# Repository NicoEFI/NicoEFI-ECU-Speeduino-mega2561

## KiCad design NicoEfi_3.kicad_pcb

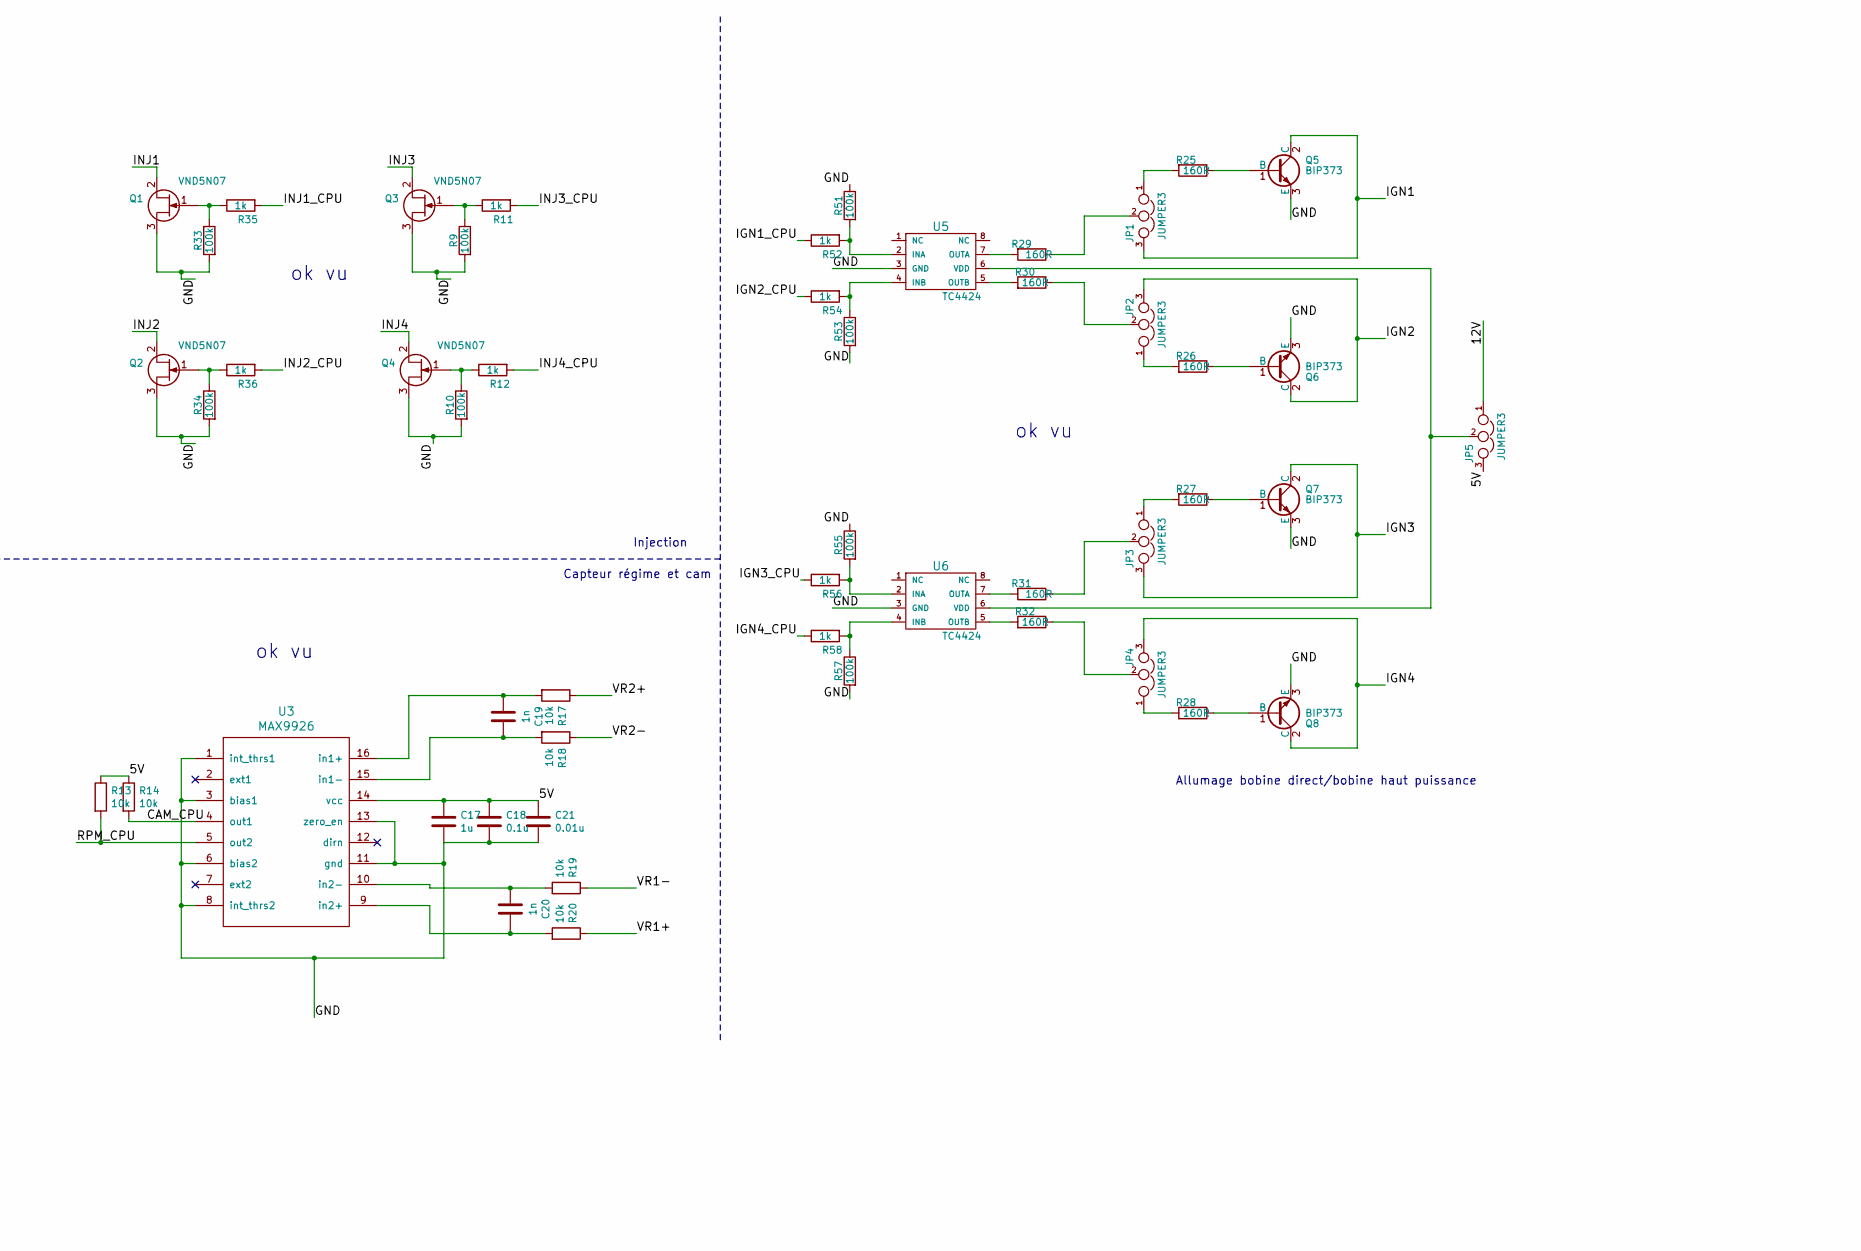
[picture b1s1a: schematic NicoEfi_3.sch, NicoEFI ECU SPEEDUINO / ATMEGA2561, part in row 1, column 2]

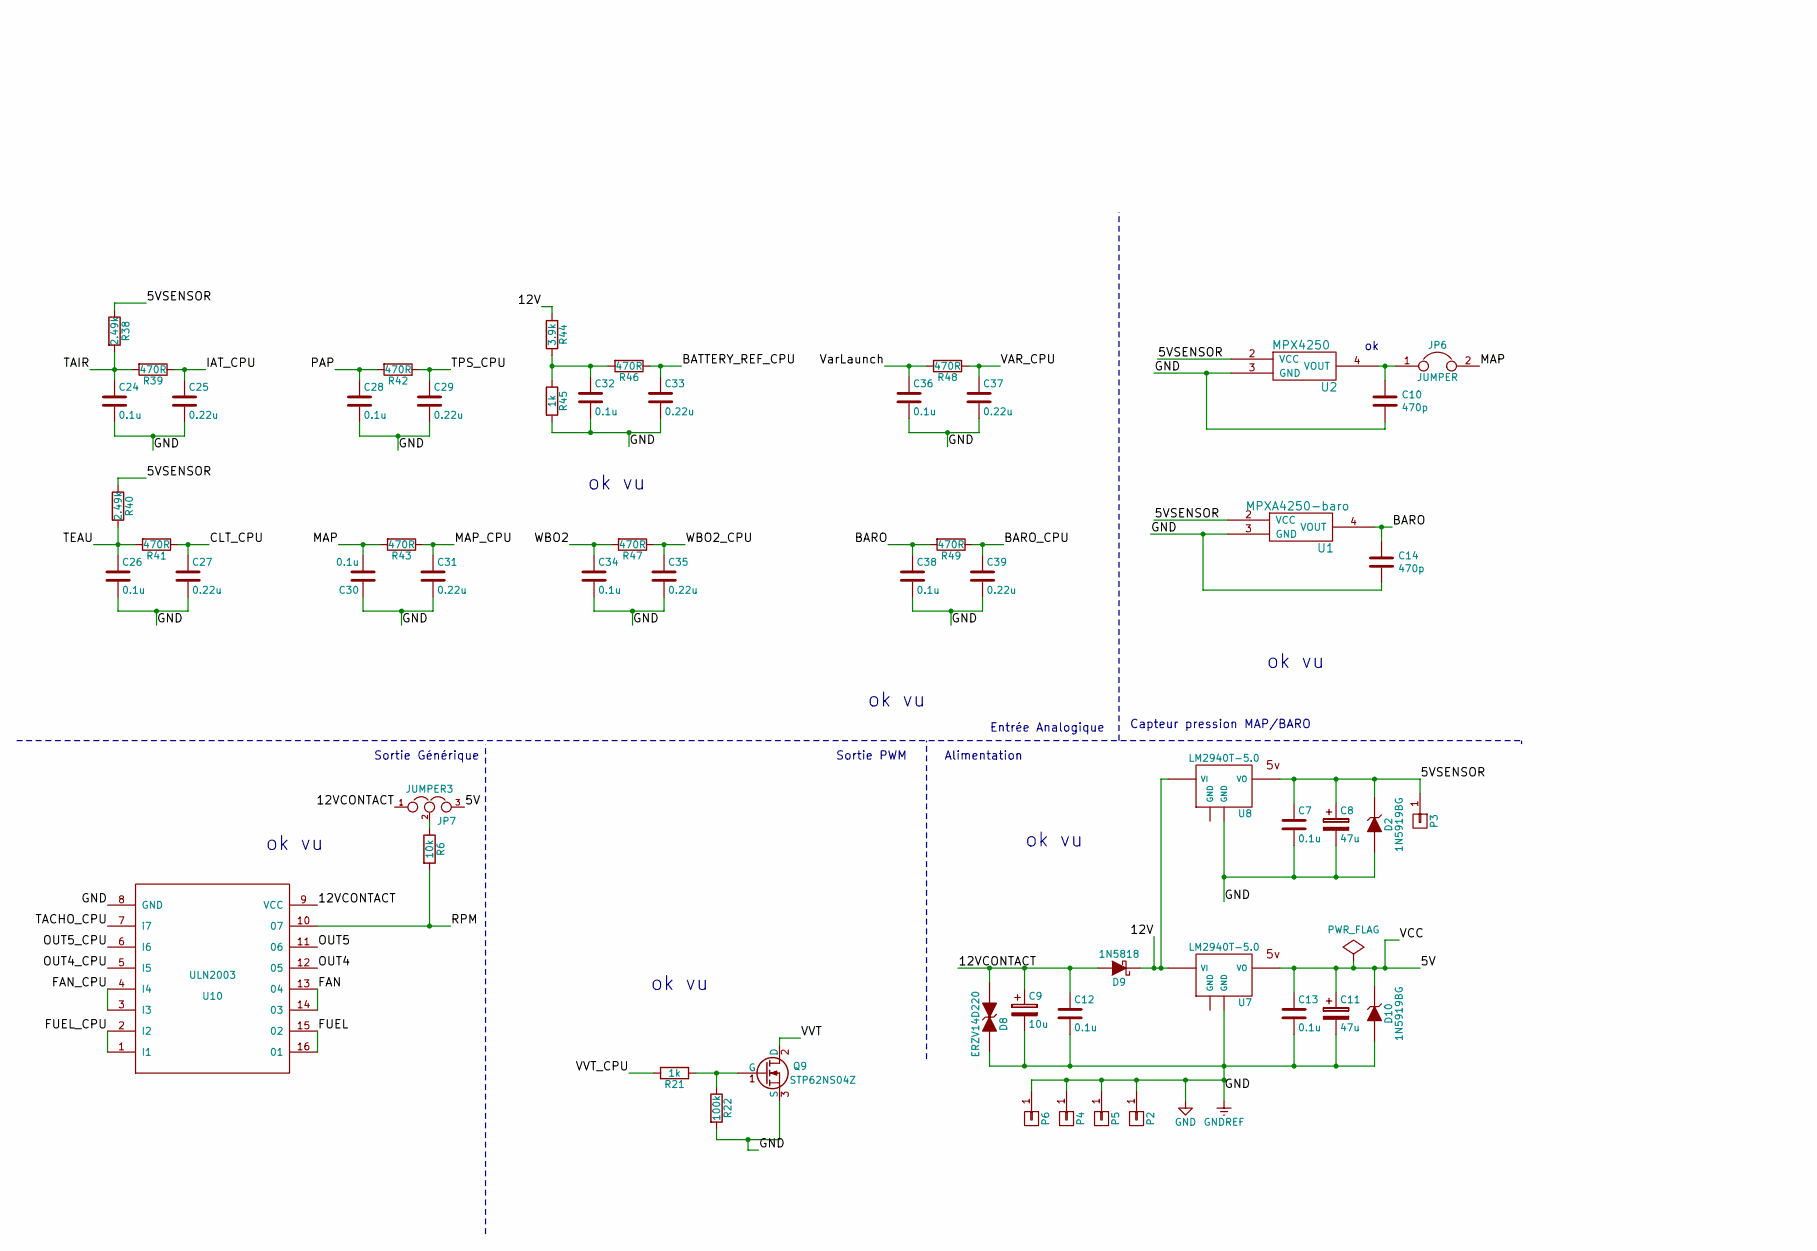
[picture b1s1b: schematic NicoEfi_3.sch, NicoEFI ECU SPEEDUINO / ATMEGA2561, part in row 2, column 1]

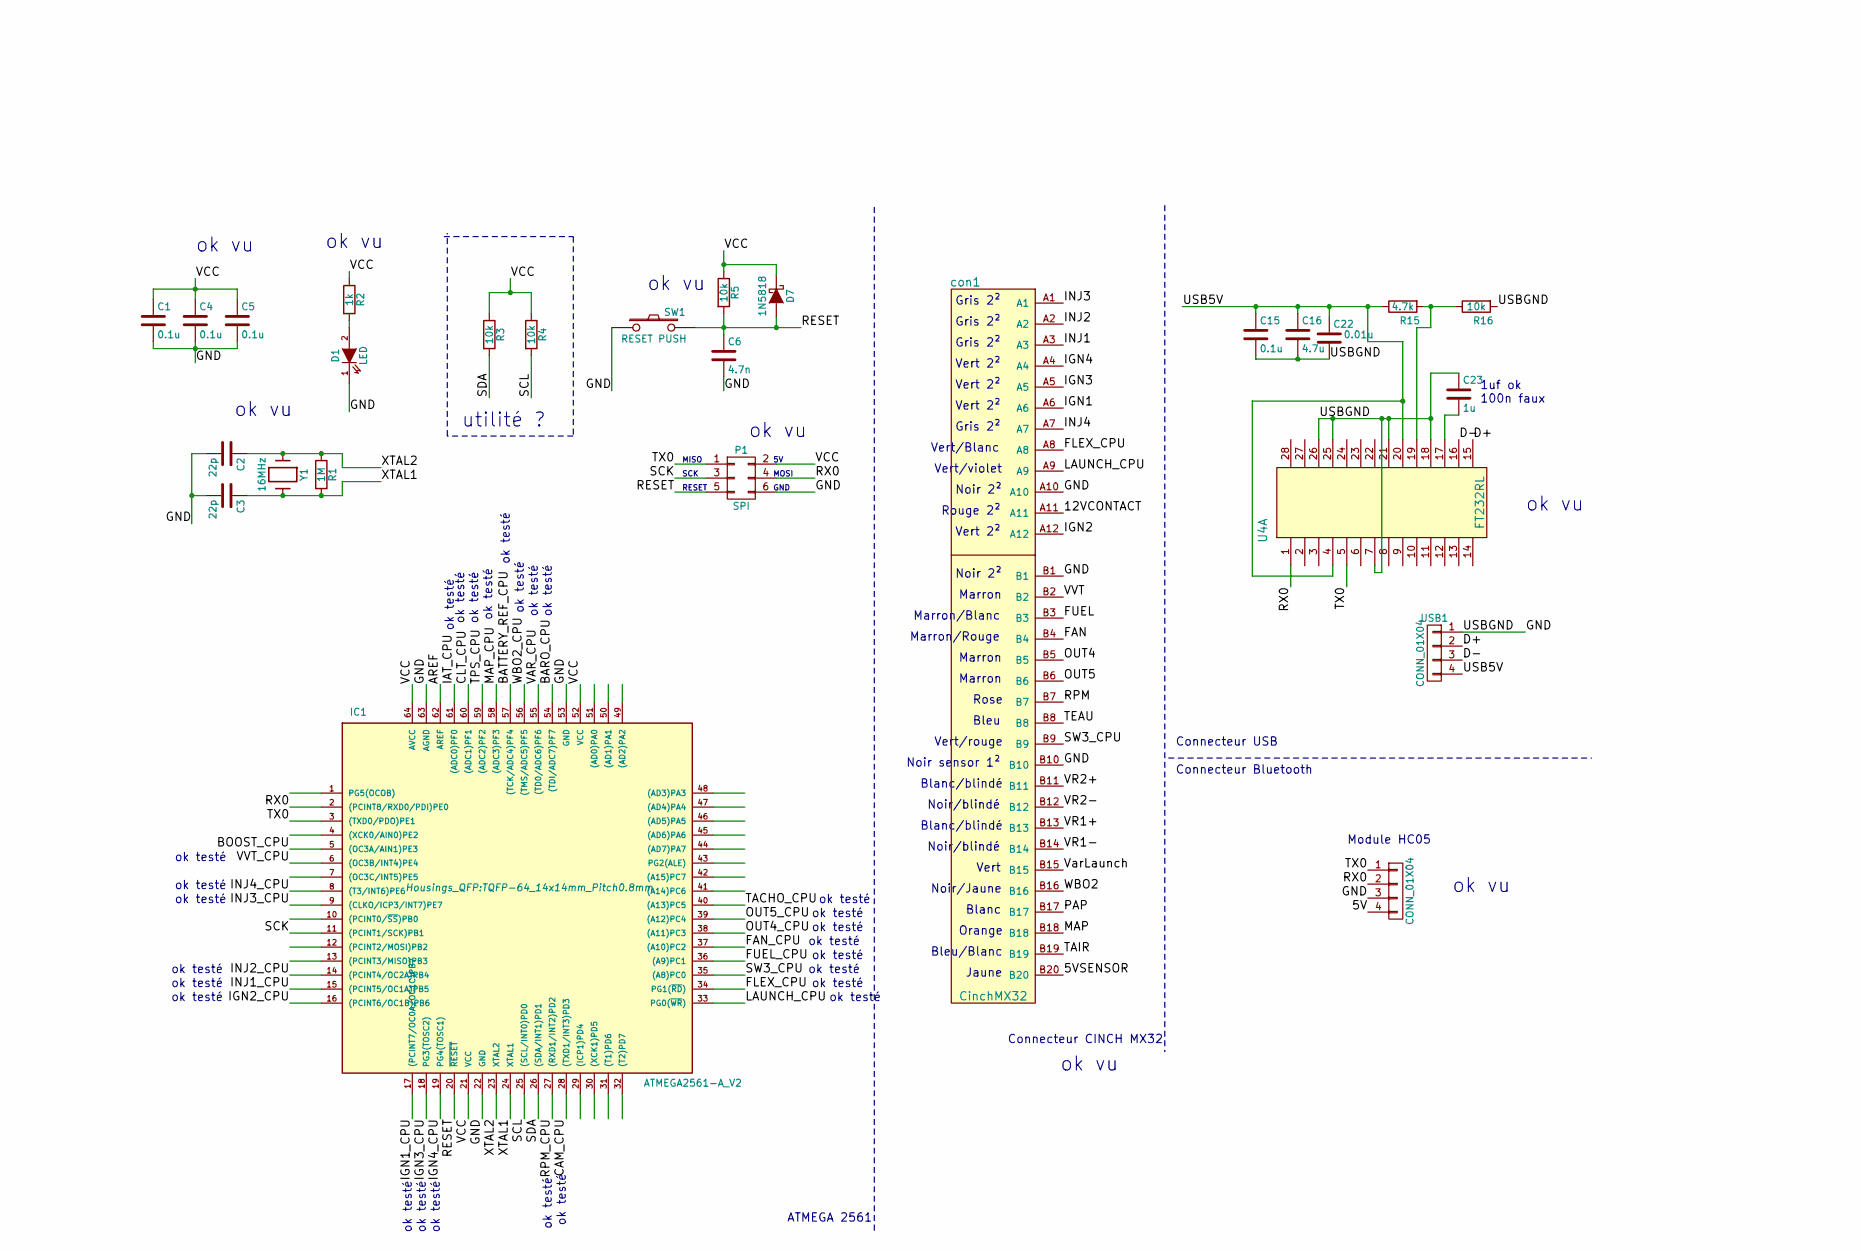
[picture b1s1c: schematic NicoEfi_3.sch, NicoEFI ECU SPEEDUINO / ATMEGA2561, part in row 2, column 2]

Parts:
C1, C4, C5, C7, C12, C13, C15, C18, C24, C26, C28, C30, C32, C34, C36, C38: 0.1u; C_1206_HandSoldering
C2, C3: 22p; C_1206_HandSoldering
C6: 4.7n; C_1206_HandSoldering
C8, C11: 47u; TantalC_SizeC_EIA-6032
C9: 10u; TantalC_SizeC_EIA-6032
C10, C14: 470p; C_1206_HandSoldering
C16: 4.7u; C_1206_HandSoldering
C17, C23: 1u; C_1206_HandSoldering
C19, C20: 1n; C_1206_HandSoldering
C21, C22: 0.01u; C_1206_HandSoldering
C25, C27, C29, C31, C33, C35, C37, C39: 0.22u; C_1206_HandSoldering
D1: LED; LED_1206
D2, D10: 1N5919BG; do214ac
D7, D9: 1N5818; SOD-123
D8: ERZV14D220; C_Disc_D7.5_P5
HC5: CONN_01X04; Pin_Header_Straight_1x04
IC1: ATMEGA2561-A_V2; TQFP-64_14x14mm_Pitch0.8mm
JP1, JP2, JP3, JP4, JP5, JP7: JUMPER3; Pin_Header_Straight_1x03
JP6: JUMPER; Pin_Header_Straight_1x02
P1: SPI; Pin_Header_Straight_2x03
P2, P3: CONN_01X01; SolderWirePad_2x_0-8mmDrill
P4, P5, P6: CONN_01X01; SolderWirePad_single_0-8mmDrill
Q1, Q2, Q3, Q4: VND5N07
Q5, Q6, Q7, Q8: BIP373; TO-220_Neutral123_Vertical
Q9: STP62NS04Z; TO-220_Neutral123_Vertical
R1: 1M; R_1206_HandSoldering
R2, R11, R12, R21, R35, R36, R45, R52, R54, R56, R58: 1k; R_1206_HandSoldering
R3, R4, R5, R6, R13, R14, R16: 10k; R_1206_HandSoldering
R9, R10, R22, R33, R34, R51, R53, R55, R57: 100k; R_1206_HandSoldering
R15: 4.7k; R_1206_HandSoldering
R17, R18, R19, R20: 10k; R_2010_HandSoldering
R25, R26, R27, R28, R29, R30, R31, R32: 160R; R_2010_HandSoldering
R38, R40: 2.49k; R_1206_HandSoldering
R39, R41, R42, R43, R46, R47, R48, R49: 470R; R_1206_HandSoldering
R44: 3.9k; R_1206_HandSoldering
SW1: RESET PUSH; smd_push
U1: MPXA4250-baro; MPXA4250_baro
U2: MPX4250; MPXA4250
U3: MAX9926; QSOP-16_3.9x4.9mm_Pitch0.635mm
U4: FT232RL; SSOP-28_5.3x10.2mm_Pitch0.65mm
U5, U6: TC4424; SOIC-8_3.9x4.9mm_Pitch1.27mm
U7, U8: LM2940T-5.0; sot223
U10: ULN2003; SOIC-16_3.9x9.9mm_Pitch1.27mm
USB1: CONN_01X04; Pin_Header_Straight_1x04
Y1: 16MHz; Crystal_HC-49_smd_11.1_3.8
con1: CinchMX32

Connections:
/5V: C1.1, C4.1, C5.1, C11.1, C13.1, C17.1, C18.1, C21.1, D7.1 (K), D10.1 (K), HC5.4, IC1.21 (VCC), IC1.52 (VCC), IC1.64 (AVCC), JP5.3, JP7.3, P1.2, R2.1, R3.1, R4.1, R5.1, R13.1, R14.1, U3.14 (vcc), U7.3 (VO)
/5VSENSOR: C7.1, C8.1, D2.1 (K), P3.1, R38.1, R40.1, U1.2 (VCC), U2.2 (VCC), U8.3 (VO), con1.B20
/12V: D9.1 (K), JP5.1, R44.1, U7.1 (VI), U8.1 (VI)
/12VCONTACT: C9.1, C12.1, D8.1 (K), D9.2 (A), JP7.1, U10.9 (VCC), con1.A11
/BARO: C14.1, C38.1, R49.2, U1.4 (VOUT)
/BARO_CPU: C39.1, IC1.54 ((TDI/ADC7)PF7), R49.1
/BATTERY_REF_CPU: C33.1, IC1.57 ((TCK/ADC4)PF4), R46.1
/CAM_CPU: IC1.28 ((TXD1/INT3)PD3), R14.2, U3.4 (out1)
/CLT_CPU: C27.1, IC1.60 ((ADC1)PF1), R41.1
/D+: U4.15, USB1.2
/D-: U4.16, USB1.3
/FAN: U10.13 (04), U10.14 (03), con1.B4
/FAN_CPU: IC1.37 ((A10)PC2), U10.3 (I3), U10.4 (I4)
/FLEX_CPU: IC1.34 (PG1(~RD~)), con1.A8
/FUEL: U10.15 (02), U10.16 (01), con1.B3
/FUEL_CPU: IC1.36 ((A9)PC1), U10.1 (I1), U10.2 (I2)
/IAT_CPU: C25.1, IC1.61 ((ADC0)PF0), R39.1
/IGN1: JP1.3, Q5.2 (C), con1.A6
/IGN1_CPU: IC1.17 ((PCINT7/OC0A/OC1C)PB7), R52.1
/IGN2: JP2.3, Q6.2 (C), con1.A12
/IGN2_CPU: IC1.16 ((PCINT6/OC1B)PB6), R54.1
/IGN3: JP3.3, Q7.2 (C), con1.A5
/IGN3_CPU: IC1.18 (PG3(TOSC2)), R56.1
/IGN4: JP4.3, Q8.2 (C), con1.A4
/IGN4_CPU: IC1.19 (PG4(TOSC1)), R58.1
/INJ1: Q1.2 (D), con1.A3
/INJ1_CPU: IC1.15 ((PCINT5/OC1A)PB5), R35.2
/INJ2: Q2.2 (D), con1.A2
/INJ2_CPU: IC1.14 ((PCINT4/OC2A)PB4), R36.2
/INJ3: Q3.2 (D), con1.A1
/INJ3_CPU: IC1.9 ((CLKO/ICP3/INT7)PE7), R11.2
/INJ4: Q4.2 (D), con1.A7
/INJ4_CPU: IC1.8 ((T3/INT6)PE6), R12.2
/LAUNCH_CPU: IC1.33 (PG0(~WR~)), con1.A9
/MAP: C30.2, JP6.2, R43.2, con1.B18
/MAP_CPU: C31.1, IC1.58 ((ADC3)PF3), R43.1
/OUT4: U10.12 (05), con1.B5
/OUT4_CPU: IC1.38 ((A11)PC3), U10.5 (I5)
/OUT5: U10.11 (06), con1.B6
/OUT5_CPU: IC1.39 ((A12)PC4), U10.6 (I6)
/PAP: C28.1, R42.2, con1.B17
/RESET: C6.1, D7.2 (A), IC1.20 (~RESET), P1.5, R5.2, SW1.2
/RPM: R6.2, U10.10 (07), con1.B7
/RPM_CPU: IC1.27 ((RXD1/INT2)PD2), R13.2, U3.5 (out2)
/RX0: HC5.2, IC1.2 ((PCINT8/RXD0/PDI)PE0), P1.4, U4.1
/SCK: IC1.11 ((PCINT1/SCK)PB1), P1.3
/SCL: IC1.25 ((SCL/INT0)PD0), R4.2
/SDA: IC1.26 ((SDA/INT1)PD1), R3.2
/SW3_CPU: IC1.35 ((A8)PC0), con1.B9
/TACHO_CPU: IC1.40 ((A13)PC5), U10.7 (i7)
/TAIR: C24.1, R38.2, R39.2, con1.B19
/TEAU: C26.1, R40.2, R41.2, con1.B8
/TPS_CPU: C29.1, IC1.59 ((ADC2)PF2), R42.1
/TX0: HC5.1, IC1.3 ((TXD0/PDO)PE1), P1.1, U4.5
/USB5V: C15.1, C16.1, C22.1, R15.1, U4.4, U4.20, USB1.4
/VAR_CPU: C37.1, IC1.55 ((TD0/ADC6)PF6), R48.1
/VR1+: R20.1, con1.B13
/VR1-: R19.1, con1.B14
/VR2+: R17.1, con1.B11
/VR2-: R18.1, con1.B12
/VVT: Q9.2 (D), con1.B2
/VVT_CPU: IC1.6 ((OC3B/INT4)PE4), R21.2
/VarLaunch: C36.1, R48.2, con1.B15
/WBO2: C34.1, R47.2, con1.B16
/WBO2_CPU: C35.1, IC1.56 ((TMS/ADC5)PF5), R47.1
/XTAL1: C3.1, IC1.24 (XTAL1), R1.2, Y1.2
/XTAL2: C2.1, IC1.23 (XTAL2), R1.1, Y1.1
GND: C1.2, C2.2, C3.2, C4.2, C5.2, C6.2, C7.2, C8.2, C9.2, C10.2, C11.2, C12.2, C13.2, C14.2, C15.2, C16.2, C17.2, C18.2, C21.2, C22.2, C23.1, C24.2, C25.2, C26.2, C27.2, C28.2, C29.2, C30.1, C31.2, C32.2, C33.2, C34.2, C35.2, C36.2, C37.2, C38.2, C39.2, D1.1 (K), D2.2 (A), D8.2 (A), D10.2 (A), HC5.3, IC1.22 (GND), IC1.53 (GND), IC1.63 (AGND), P1.6, P2.1, P4.1, P5.1, P6.1, Q1.3 (S), Q2.3 (S), Q3.3 (S), Q4.3 (S), Q5.3 (E), Q6.3 (E), Q7.3 (E), Q8.3 (E), Q9.3 (S), R9.2, R10.2, R16.2, R22.2, R33.2, R34.2, R45.2, R51.1, R53.2, R55.1, R57.2, SW1.1, U1.3 (GND), U2.3 (GND), U3.1 (int_thrs1), U3.3 (bias1), U3.6 (bias2), U3.8 (int_thrs2), U3.11 (gnd), U3.13 (zero_en), U4.7, U4.18, U4.21, U4.25, U4.26, U5.3 (GND), U6.3 (GND), U7.2 (GND), U8.2 (GND), U10.8 (GND), USB1.1, con1.A10, con1.B1, con1.B10; also elsewhere on the board
unnamed: C10.1, JP6.1, U2.4 (VOUT)
unnamed: C19.1, R18.2, U3.15 (in1-)
unnamed: C19.2, R17.2, U3.16 (in1+)
unnamed: C20.1, R19.2, U3.10 (in2-)
unnamed: C20.2, R20.2, U3.9 (in2+)
unnamed: C23.2, U4.17
unnamed: C32.1, R44.2, R45.1, R46.2
unnamed: D1.2 (A), R2.2
unnamed: JP1.1, R25.2
unnamed: JP1.2, R29.1
unnamed: JP2.1, R26.2
unnamed: JP2.2, R30.1
unnamed: JP3.1, R27.2
unnamed: JP3.2, R31.1
unnamed: JP4.1, R28.2
unnamed: JP4.2, R32.1
unnamed: JP5.2, U5.6 (VDD), U6.6 (VDD)
unnamed: JP7.2, R6.1
unnamed: Q1.1 (G), R33.1, R35.1
unnamed: Q2.1 (G), R34.1, R36.1
unnamed: Q3.1 (G), R9.1, R11.1
unnamed: Q4.1 (G), R10.1, R12.1
unnamed: Q5.1 (B), R25.1
unnamed: Q6.1 (B), R26.1
unnamed: Q7.1 (B), R27.1
unnamed: Q8.1 (B), R28.1
unnamed: Q9.1 (G), R21.1, R22.1
unnamed: R15.2, R16.1, U4.19
unnamed: R29.2, U5.7 (OUTA)
unnamed: R30.2, U5.5 (OUTB)
unnamed: R31.2, U6.7 (OUTA)
unnamed: R32.2, U6.5 (OUTB)
unnamed: R51.2, R52.2, U5.2 (INA)
unnamed: R53.1, R54.2, U5.4 (INB)
unnamed: R55.2, R56.2, U6.2 (INA)
unnamed: R57.1, R58.2, U6.4 (INB)

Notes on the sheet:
Capteur pression MAP/BARO
Injection
Capteur régime et cam
Allumage bobine direct/bobine haut puissance
MISO
MOSI
GND
SCK
RESET
Connecteur USB
Connecteur Bluetooth
Module HC05
Connecteur CINCH MX32
ATMEGA 2561
Alimentation
Sortie PWM
Sortie Générique
Entrée Analogique
ok vu
utilité ?
Gris 2²
Rose
Vert 2²
Rouge 2²
Noir 2²
Jaune
Noir sensor 1²
Marron/Rouge
Marron/Blanc
Marron
Vert/violet
Vert/Blanc
Bleu/Blanc
Bleu
Orange
Blanc
Vert
Blanc/blindé
Noir/blindé
Vert/rouge

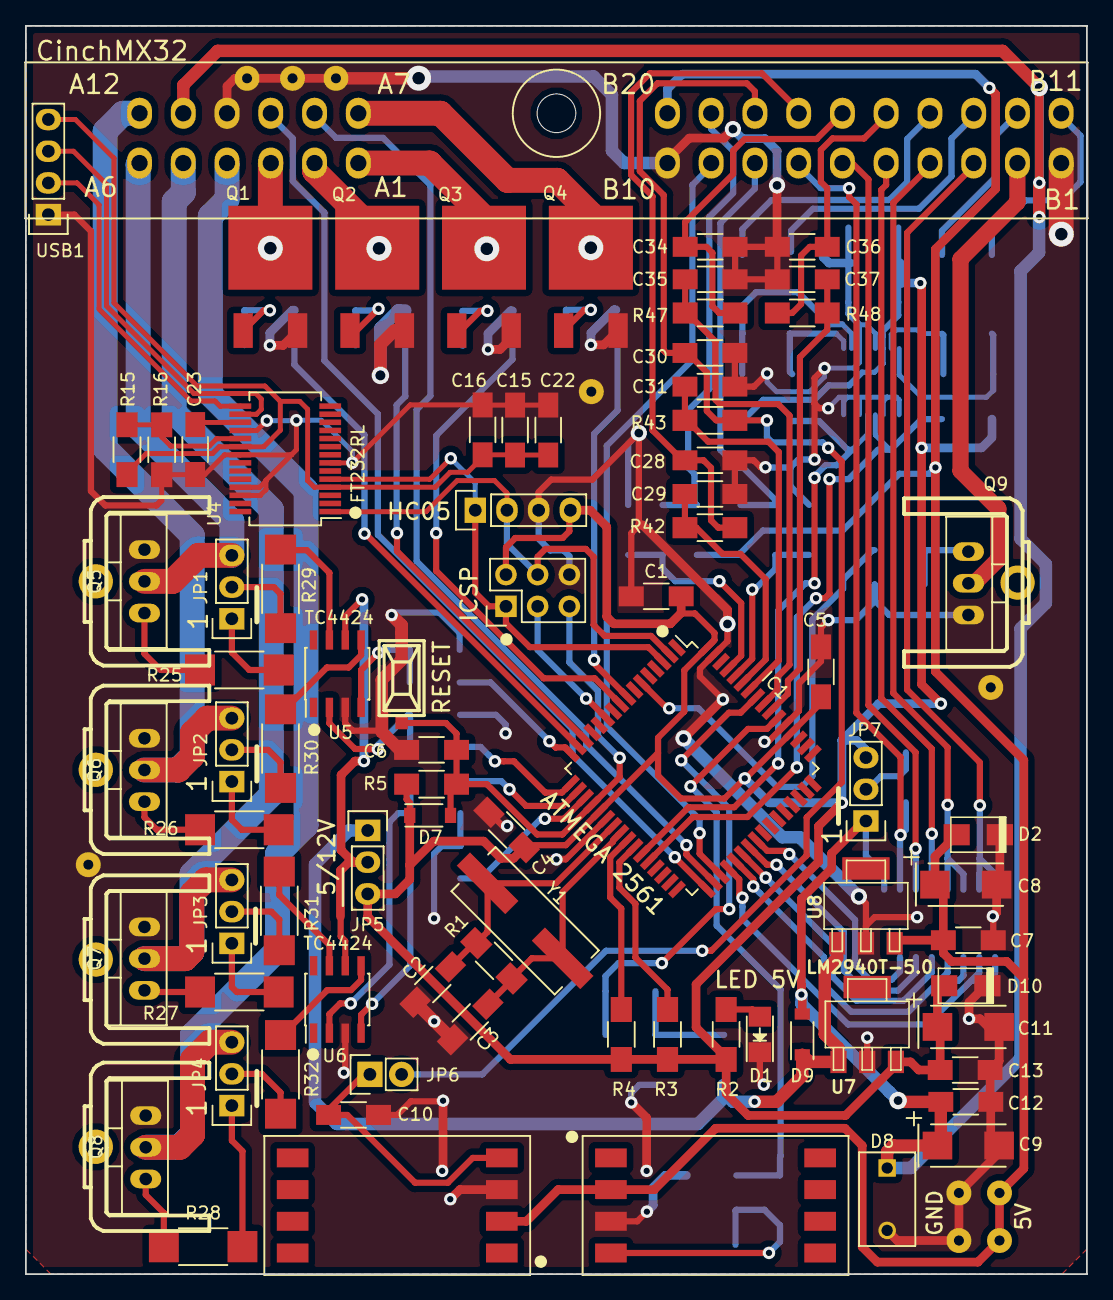
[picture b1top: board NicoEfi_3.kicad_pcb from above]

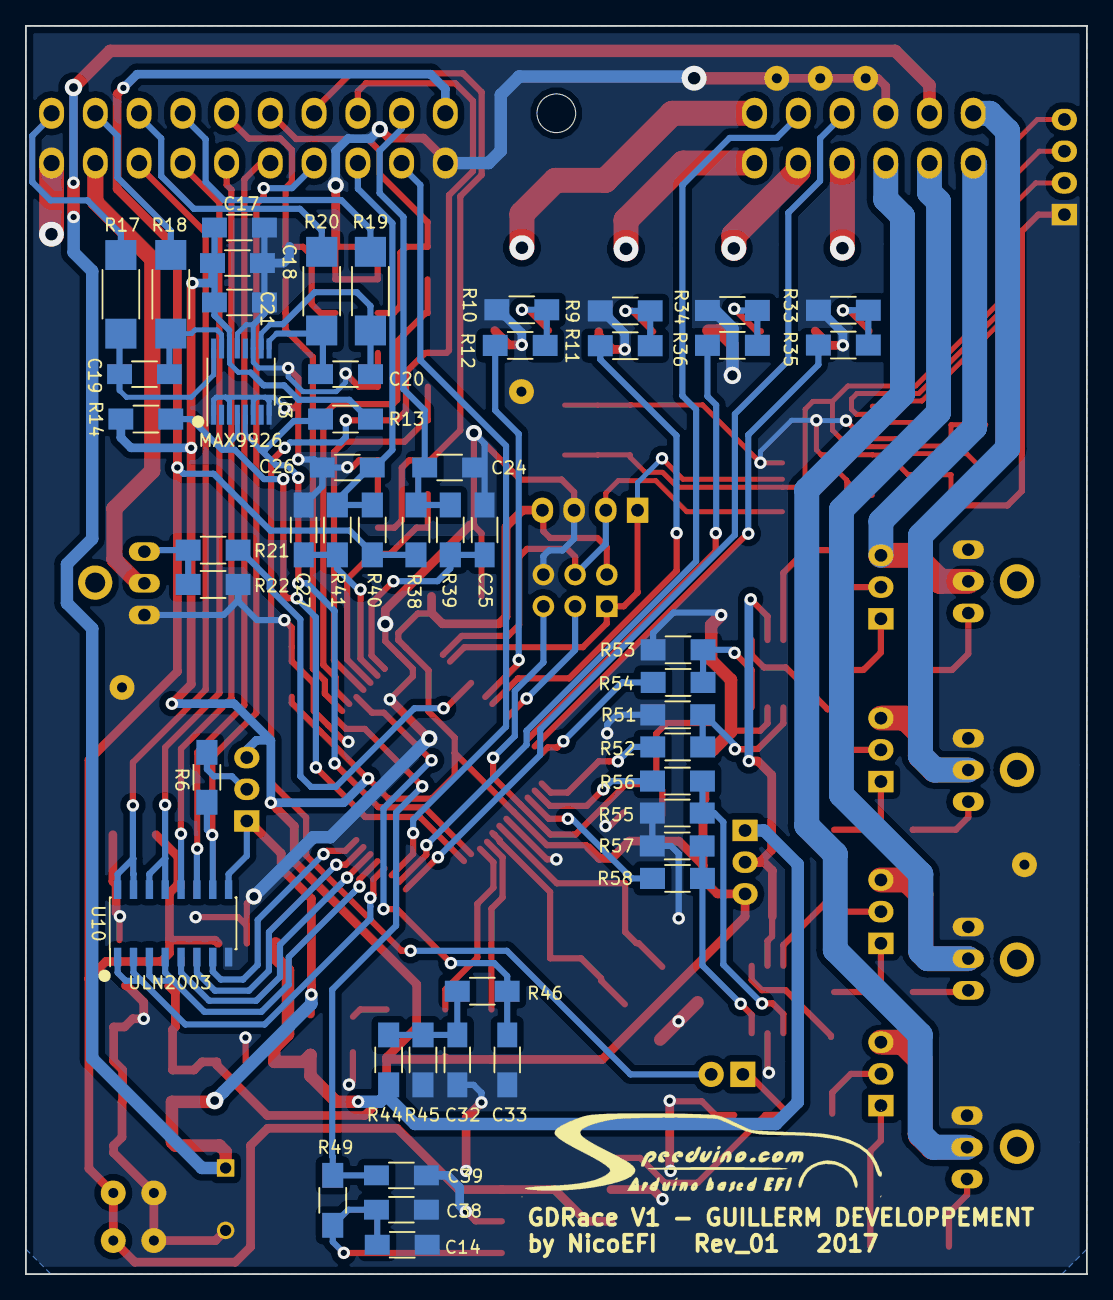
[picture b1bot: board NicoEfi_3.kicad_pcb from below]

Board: 2 copper layers, 85.0 x 100.0 mm, 142 parts (49 on the bottom side), 104 nets.

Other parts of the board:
P4#2, P4#3, P4#4: CONN_01X01; SolderWirePad_single_0-8mmDrill
hs_5770, hs_5770#2, hs_5770#3, hs_5770#4, hs_5770#5: VAL***; hs_5771

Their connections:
GND: P4#2.1, P4#3.1, P4#4.1; also elsewhere on the board

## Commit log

2019-12-02 Add files via upload
    NOT TESTED
